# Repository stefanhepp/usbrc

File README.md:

USB RC Receiver
---------------

USB RC receiver to be used as wireless controller for RC flight sims.

Based on ESP32, supports multiple protocols:
* S.BUS (FrSky)
* SRXL2 (Spektrum)

The SRXL2 protocol implementation is based on the SpektrmRC SRXL2 implementation:
https://github.com/SpektrumRC/SRXL2.git

License
-------
Shield: [![CC BY-SA 4.0][cc-by-sa-shield]][cc-by-sa]

This work is licensed under a
[Creative Commons Attribution-ShareAlike 4.0 International License][cc-by-sa].

[![CC BY-SA 4.0][cc-by-sa-image]][cc-by-sa]

[cc-by-sa]: http://creativecommons.org/licenses/by-sa/4.0/
[cc-by-sa-image]: https://licensebuttons.net/l/by-sa/4.0/88x31.png
[cc-by-sa-shield]: https://img.shields.io/badge/License-CC%20BY--SA%204.0-lightgrey.svg

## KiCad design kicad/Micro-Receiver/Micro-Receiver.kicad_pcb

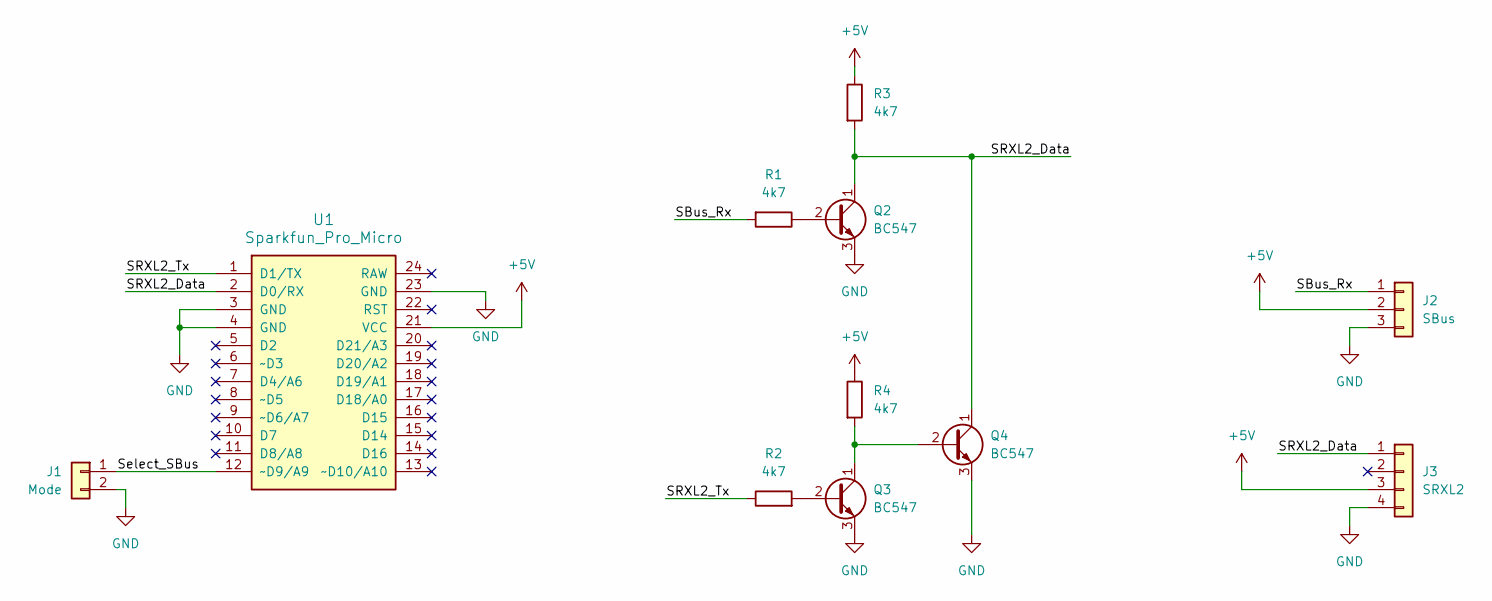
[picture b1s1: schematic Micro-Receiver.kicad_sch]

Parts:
J1: Mode; PinHeader_1x02_P2.54mm_Vertical
J2: SBus; PinHeader_1x03_P2.54mm_Vertical
J3: SRXL2; PinHeader_1x04_P2.54mm_Vertical
Q2, Q3, Q4: BC547; TO-92L_Inline_Wide
R1, R3, R4: 4k7; R_Axial_DIN0309_L9.0mm_D3.2mm_P5.08mm_Vertical
R2: 4k7; R_Axial_DIN0309_L9.0mm_D3.2mm_P2.54mm_Vertical
U1: Sparkfun_Pro_Micro

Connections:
+5V: J2.2, J3.3, R3.1, R4.1, U1.21 (VCC)
/SBus_Rx: J2.1, R1.2
/SRXL2_Data: J3.1, Q2.1 (C), Q4.1 (C), R3.2, U1.2 (D0/RX)
/SRXL2_Tx: R2.1, U1.1 (D1/TX)
/Select_SBus: J1.1, U1.12 (~D9/A9)
GND: J1.2, J2.3, J3.4, Q2.3 (E), Q3.3 (E), Q4.3 (E), U1.3 (GND), U1.4 (GND), U1.23 (GND)
unnamed: Q2.2 (B), R1.1
unnamed: Q3.2 (B), R2.2
unnamed: Q3.1 (C), Q4.2 (B), R4.2

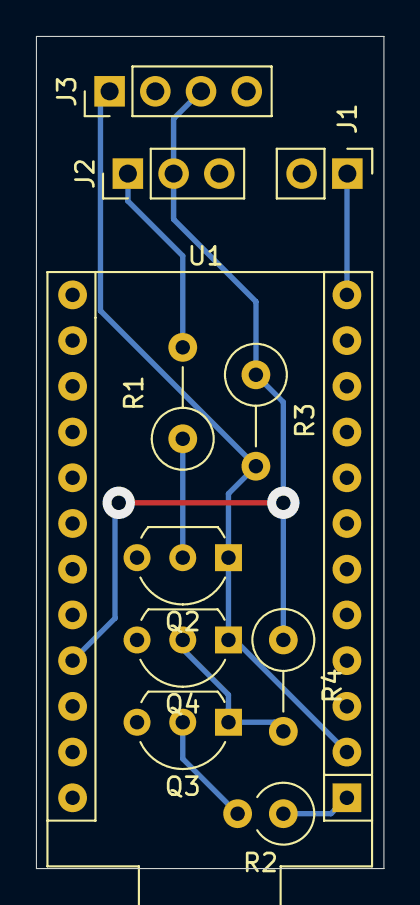
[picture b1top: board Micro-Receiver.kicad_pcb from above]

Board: 2 copper layers, 19.3 x 46.2 mm, 11 parts (0 on the bottom side), 9 nets.

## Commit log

2025-10-25 First version of SRXL2 decoder
2025-10-26 Working version with SRXL2 and SBUS on Arduino Micro
2025-10-30 Added schematic and layout for Micro SBus/SRXL adapter
2026-03-26 Do not send when TX is not connected, to let the computer sleep
